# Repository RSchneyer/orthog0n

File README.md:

# orthog0n

The orthog0n is the last keyboard I'll probably design (for the forseeable future). The RGBKB Zen that I had been using for games for like 5 years bit the dust, so I decided to throw together something I had always wanted to get around to making.

As usual, I take no responsibility for anything that doesn't work, or goes wrong when you try to build or use this board. Good luck!

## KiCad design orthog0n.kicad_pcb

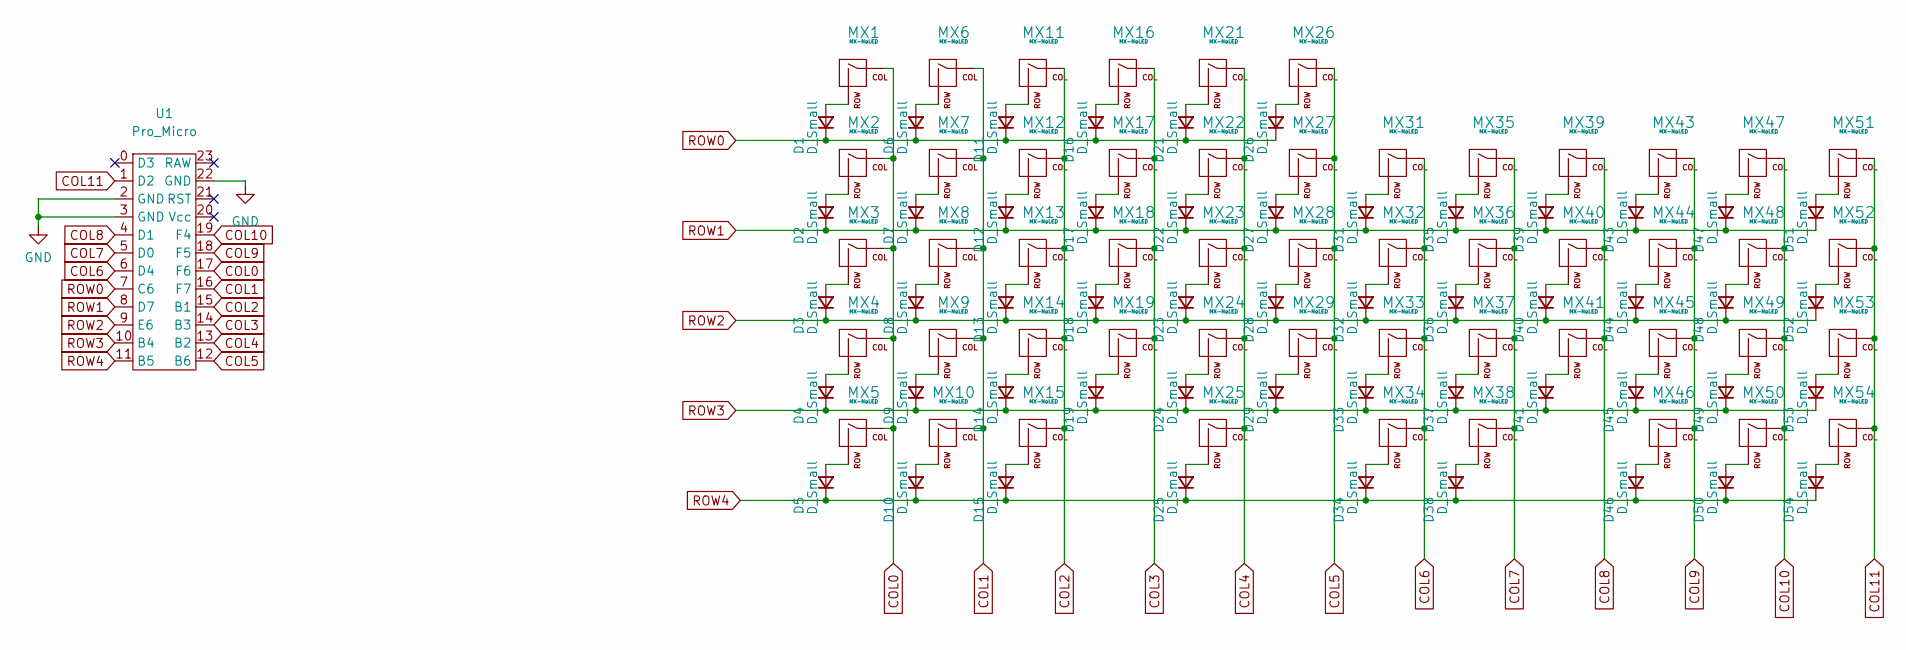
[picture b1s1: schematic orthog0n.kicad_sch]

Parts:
D1, D2, D3, D4, D5, D6, D7, D8, D9, D10, D11, D12, D13, D14, D15, D16, D17, D18, D19, D21, D22, D23, D24, D25, D26, D27, D28, D29, D31, D32, D33, D34, D35, D36, D37, D38, D39, D40, D41, D43, D44, D45, D46, D47, D48, D49, D50, D51, D52, D53, D54: D_Small; D_DO-35_SOD27_P10.16mm_Horizontal
MX1, MX2, MX3, MX4, MX5, MX15, MX46, MX51, MX52, MX53, MX54: MX-NoLED; SW_Cherry_MX_1.50u_PCB
MX6, MX7, MX8, MX9, MX10, MX11, MX12, MX13, MX14, MX16, MX17, MX18, MX19, MX21, MX22, MX23, MX24, MX26, MX27, MX28, MX29, MX31, MX32, MX33, MX34, MX35, MX36, MX37, MX39, MX40, MX41, MX43, MX44, MX45, MX47, MX48, MX49, MX50: MX-NoLED; SW_Cherry_MX_1.00u_PCB
MX25, MX38: MX-NoLED; SW_Cherry_MX_2.00u_PCB
U1: Pro_Micro; pro_micro

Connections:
COL0: MX1.1 (COL), MX2.1 (COL), MX3.1 (COL), MX4.1 (COL), MX5.1 (COL), U1.17 (F6)
COL1: MX6.1 (COL), MX7.1 (COL), MX8.1 (COL), MX9.1 (COL), MX10.1 (COL), U1.16 (F7)
COL2: MX11.1 (COL), MX12.1 (COL), MX13.1 (COL), MX14.1 (COL), MX15.1 (COL), U1.15 (B1)
COL3: MX16.1 (COL), MX17.1 (COL), MX18.1 (COL), MX19.1 (COL), U1.14 (B3)
COL4: MX21.1 (COL), MX22.1 (COL), MX23.1 (COL), MX24.1 (COL), MX25.1 (COL), U1.13 (B2)
COL5: MX26.1 (COL), MX27.1 (COL), MX28.1 (COL), MX29.1 (COL), U1.12 (B6)
COL6: MX31.1 (COL), MX32.1 (COL), MX33.1 (COL), MX34.1 (COL), U1.6 (D4)
COL7: MX35.1 (COL), MX36.1 (COL), MX37.1 (COL), MX38.1 (COL), U1.5 (D0)
COL8: MX39.1 (COL), MX40.1 (COL), MX41.1 (COL), U1.4 (D1)
COL9: MX43.1 (COL), MX44.1 (COL), MX45.1 (COL), MX46.1 (COL), U1.18 (F5)
COL10: MX47.1 (COL), MX48.1 (COL), MX49.1 (COL), MX50.1 (COL), U1.19 (F4)
COL11: MX51.1 (COL), MX52.1 (COL), MX53.1 (COL), MX54.1 (COL), U1.1 (D2)
GND: U1.2 (GND), U1.3 (GND), U1.22 (GND)
unnamed: D1.2 (A), MX1.2 (ROW)
unnamed: D2.2 (A), MX2.2 (ROW)
unnamed: D3.2 (A), MX3.2 (ROW)
unnamed: D4.2 (A), MX4.2 (ROW)
unnamed: D5.2 (A), MX5.2 (ROW)
unnamed: D6.2 (A), MX6.2 (ROW)
unnamed: D7.2 (A), MX7.2 (ROW)
unnamed: D8.2 (A), MX8.2 (ROW)
unnamed: D9.2 (A), MX9.2 (ROW)
unnamed: D10.2 (A), MX10.2 (ROW)
unnamed: D11.2 (A), MX11.2 (ROW)
unnamed: D12.2 (A), MX12.2 (ROW)
unnamed: D13.2 (A), MX13.2 (ROW)
unnamed: D14.2 (A), MX14.2 (ROW)
unnamed: D15.2 (A), MX15.2 (ROW)
unnamed: D16.2 (A), MX16.2 (ROW)
unnamed: D17.2 (A), MX17.2 (ROW)
unnamed: D18.2 (A), MX18.2 (ROW)
unnamed: D19.2 (A), MX19.2 (ROW)
unnamed: D21.2 (A), MX21.2 (ROW)
unnamed: D22.2 (A), MX22.2 (ROW)
unnamed: D23.2 (A), MX23.2 (ROW)
unnamed: D24.2 (A), MX24.2 (ROW)
unnamed: D25.2 (A), MX25.2 (ROW)
unnamed: D26.2 (A), MX26.2 (ROW)
unnamed: D27.2 (A), MX27.2 (ROW)
unnamed: D28.2 (A), MX28.2 (ROW)
unnamed: D29.2 (A), MX29.2 (ROW)
unnamed: D31.2 (A), MX31.2 (ROW)
unnamed: D32.2 (A), MX32.2 (ROW)
unnamed: D33.2 (A), MX33.2 (ROW)
unnamed: D34.2 (A), MX34.2 (ROW)
unnamed: D35.2 (A), MX35.2 (ROW)
unnamed: D36.2 (A), MX36.2 (ROW)
unnamed: D37.2 (A), MX37.2 (ROW)
unnamed: D38.2 (A), MX38.2 (ROW)
unnamed: D39.2 (A), MX39.2 (ROW)
unnamed: D40.2 (A), MX40.2 (ROW)
unnamed: D41.2 (A), MX41.2 (ROW)
unnamed: D43.2 (A), MX43.2 (ROW)
unnamed: D44.2 (A), MX44.2 (ROW)
unnamed: D45.2 (A), MX45.2 (ROW)
unnamed: D46.2 (A), MX46.2 (ROW)
unnamed: D47.2 (A), MX47.2 (ROW)
unnamed: D48.2 (A), MX48.2 (ROW)
unnamed: D49.2 (A), MX49.2 (ROW)
unnamed: D50.2 (A), MX50.2 (ROW)
unnamed: D51.2 (A), MX51.2 (ROW)
unnamed: D52.2 (A), MX52.2 (ROW)
unnamed: D53.2 (A), MX53.2 (ROW)
unnamed: D54.2 (A), MX54.2 (ROW)
ROW0: D1.1 (K), D6.1 (K), D11.1 (K), D16.1 (K), D21.1 (K), D26.1 (K), U1.7 (C6)
ROW1: D2.1 (K), D7.1 (K), D12.1 (K), D17.1 (K), D22.1 (K), D27.1 (K), D31.1 (K), D35.1 (K), D39.1 (K), D43.1 (K), D47.1 (K), D51.1 (K), U1.8 (D7)
ROW2: D3.1 (K), D8.1 (K), D13.1 (K), D18.1 (K), D23.1 (K), D28.1 (K), D32.1 (K), D36.1 (K), D40.1 (K), D44.1 (K), D48.1 (K), D52.1 (K), U1.9 (E6)
ROW3: D4.1 (K), D9.1 (K), D14.1 (K), D19.1 (K), D24.1 (K), D29.1 (K), D33.1 (K), D37.1 (K), D41.1 (K), D45.1 (K), D49.1 (K), D53.1 (K), U1.10 (B4)
ROW4: D5.1 (K), D10.1 (K), D15.1 (K), D25.1 (K), D34.1 (K), D38.1 (K), D46.1 (K), D50.1 (K), D54.1 (K), U1.11 (B5)

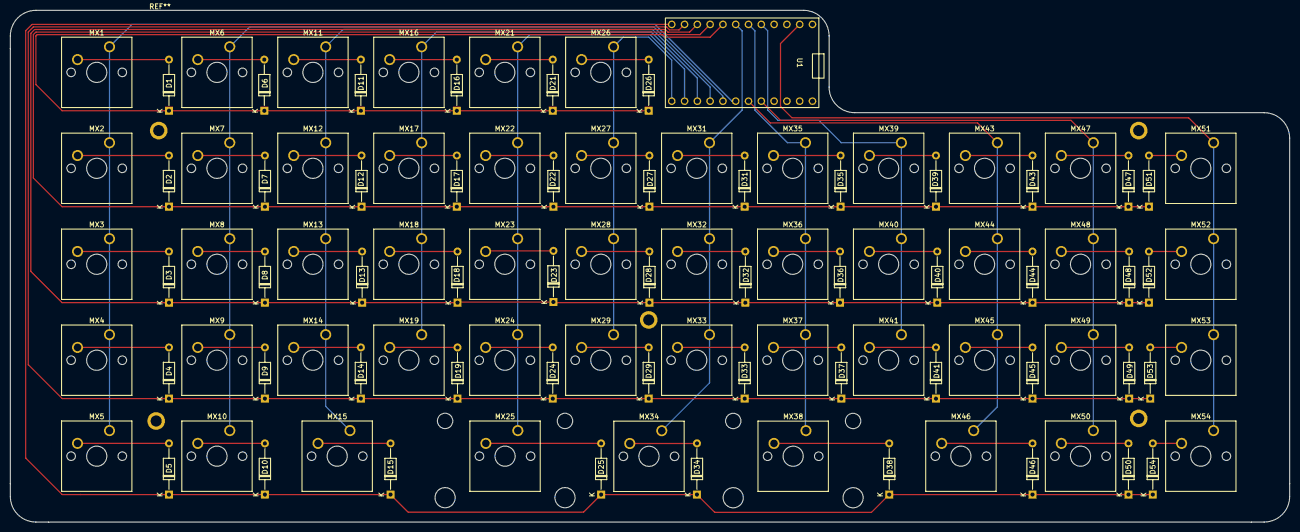
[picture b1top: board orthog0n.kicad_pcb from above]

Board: 2 copper layers, 254.0 x 101.6 mm, 103 parts (0 on the bottom side), 69 nets.

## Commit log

2023-12-28 upload everything
2023-12-28 Added "firmware"
2023-12-28 Rename code/py to code.py
